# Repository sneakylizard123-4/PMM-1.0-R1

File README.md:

# PMM-1.0-R1 (Power Management Module)

A USB-C battery management module with charging, fuel gauging, and a switched 5V output.

## Custom Features

- BQ25895 2A buck charger with I2C control
- BQ27441-G1 fuel gauge
- TPS61089 boost converter for 5V output
- TPS22917 load
- TLV75733 3.3V LDO
- STM32C031C4T6 MCU
- 4-layer PCB, 50x30mm

## PCB Design

this board is designed to fit on a breadboard without much hassle
it is a 4-layer pcb with an inner ground layer

## Firmware

PlatformIO project using internal 48MHz oscillator (no crystal).

- I2C1 (PA9/PA10): BQ25895 charger at 0x6B, BQ27441 fuel gauge at 0x55
- USART2 (PA2/PA3): 115200 debug/status output
- ADC1 (PA8): VBUS monitoring
- GPIO: load switch (PA0), charger CE (PA4), LED (PA6), SHDN (PA11), FORCE_ON (PA12)

Flash with PlatformIO:

```
pio run -t upload
```

## BOM (Bill of Materials)

| Ref | Value | LCSC # | MPN | Manufacturer | Footprint | Qty | Unit $ | Ext $ | Link |
|-----|-------|--------|-----|--------------|-----------|-----|--------|-------|------|
| C1-C3,C8,C10 | 47uF 1210 16V X5R | C6783889 | 1210X476M160CT | Walsin | 1210 | 5 | 0.0900 | 0.4500 | [LCSC](https://www.lcsc.com/product-detail/C6783889.html) |
| C4,C7,C14,C27,C29 | 100nF 0402 25V X7R | C56392 | 0402B104K250NT | FH(Guangdong Fenghua) | 0402 | 5 | 0.0115 | 0.0575 | [LCSC](https://www.lcsc.com/product-detail/C56392.html) |
| C5 | 100nF 0805 50V X7R | C83055 | 0805B104K500CT | Walsin | 0805 | 1 | 0.0100 | 0.0100 | [LCSC](https://www.lcsc.com/product-detail/C83055.html) |
| C6,C22,C23,C28 | 10uF 0603 10V X5R | C19702 | CL10A106KP8NNNC | Samsung | 0603 | 4 | 0.0065 | 0.0260 | [LCSC](https://www.lcsc.com/product-detail/C19702.html) |
| C9 | 24pF 0402 C0G | C2242874 | C0402C240J4GACTU | KEMET | 0402 | 1 | 0.0100 | 0.0100 | [LCSC](https://www.lcsc.com/product-detail/C2242874.html) |
| C11 | 560pF 0402 C0G 50V | C3895255 | C0402C0G500-561FNP | Venkel | 0402 | 1 | 0.0313 | 0.0313 | [LCSC](https://www.lcsc.com/product-detail/C3895255.html) |
| C12,C19 | 100nF 0805 50V X7R | C83055 | 0805B104K500CT | Walsin | 0805 | 2 | 0.0100 | 0.0200 | [LCSC](https://www.lcsc.com/product-detail/C83055.html) |
| C13,C18 | 10uF 0805 10V X7R | C396720 | 0805B106K100CT | Walsin | 0805 | 2 | 0.0950 | 0.1900 | [LCSC](https://www.lcsc.com/product-detail/C396720.html) |
| C15 | 47uF 0805 10V X5R | C6119904 | CGA0805X5R476M100MT | HRE | 0805 | 1 | 0.1000 | 0.1000 | [LCSC](https://www.lcsc.com/product-detail/C6119904.html) |
| C16 | 1uF 0805 16V X7R | C2991444 | 0805B105K160CT-C | Walsin | 0805 | 1 | 0.0230 | 0.0230 | [LCSC](https://www.lcsc.com/product-detail/C2991444.html) |
| C17 | 0.47uF 0402 10V X5R | C47339 | CL05A474KP5NNNC | Samsung | 0402 | 1 | 0.0200 | 0.0200 | [LCSC](https://www.lcsc.com/product-detail/C47339.html) |
| C20 | 47nF 0603 25V X7R | C3881195 | C0603C473J3RAC7867 | KEMET | 0603 | 1 | 0.0100 | 0.0100 | [LCSC](https://www.lcsc.com/product-detail/C3881195.html) |
| C21 | 4.7uF 0402 6.3V X5R | C340648 | 0402X475M6R3CT | Walsin | 0402 | 1 | 0.0240 | 0.0240 | [LCSC](https://www.lcsc.com/product-detail/C340648.html) |
| C24,C25 | 1uF 0603 16V X7R | C106248 | CC0603KRX7R7BB105 | YAGEO | 0603 | 2 | 0.0310 | 0.0620 | [LCSC](https://www.lcsc.com/product-detail/C106248.html) |
| C26 | 100nF 0603 50V X7R | C14663 | CC0603KRX7R9BB104 | YAGEO | 0603 | 1 | 0.0100 | 0.0100 | [LCSC](https://www.lcsc.com/product-detail/C14663.html) |
| D1-D3 | LED 0603 emerald green | C7429914 | NCD0603G3 | NATIONSTAR | 0603 | 3 | 0.0080 | 0.0240 | [LCSC](https://www.lcsc.com/product-detail/C7429914.html) |
| L1 | 470nH shielded power inductor | C18221164 | XFL4015-471MEC | Coilcraft | SMD 4x4mm | 1 | 1.5000 | 1.5000 | [LCSC](https://www.lcsc.com/product-detail/C18221164.html) |
| L2 | 2.2uH shielded power inductor 8A | C122469 | XFL4020-222MEC | Coilcraft | SMD 4x4mm | 1 | 1.5000 | 1.5000 | [LCSC](https://www.lcsc.com/product-detail/C122469.html) |
| R1,R16,R19,R20 | 10k 0603 1% | C98220 | RC0603FR-0710KL | YAGEO | 0603 | 4 | 0.0100 | 0.0400 | [LCSC](https://www.lcsc.com/product-detail/C98220.html) |
| R2 | 309k 0402 1% | C171694 | RC0402FR-07309KL | YAGEO | 0402 | 1 | 0.0100 | 0.0100 | [LCSC](https://www.lcsc.com/product-detail/C171694.html) |
| R3 | 133k 0402 1% | C3015855 | SCR0402F133K | VO | 0402 | 1 | 0.0100 | 0.0100 | [LCSC](https://www.lcsc.com/product-detail/C3015855.html) |
| R4 | 28.7k 0402 1% | C185433 | RC0402FR-0728K7L | YAGEO | 0402 | 1 | 0.0100 | 0.0100 | [LCSC](https://www.lcsc.com/product-detail/C185433.html) |
| R5 | 240k 0603 1% | C137765 | RC0603FR-07240KL | YAGEO | 0603 | 1 | 0.0100 | 0.0100 | [LCSC](https://www.lcsc.com/product-detail/C137765.html) |
| R6 | 76.8k 0402 1% | C185396 | RC0402FR-0776K8L | YAGEO | 0402 | 1 | 0.0100 | 0.0100 | [LCSC](https://www.lcsc.com/product-detail/C185396.html) |
| R7 | 100k 0402 1% | C60491 | RC0402FR-07100KL | YAGEO | 0402 | 1 | 0.0060 | 0.0060 | [LCSC](https://www.lcsc.com/product-detail/C60491.html) |
| R8 | 100k 0603 1% | C14675 | RC0603FR-07100KL | YAGEO | 0603 | 1 | 0.0100 | 0.0100 | [LCSC](https://www.lcsc.com/product-detail/C14675.html) |
| R9 | 0.010 ohm 1% 2512 3W shunt | C520398 | LCSR2512FR010Q9L | RESI | 2512 | 1 | 0.1000 | 0.1000 | [LCSC](https://www.lcsc.com/product-detail/C520398.html) |
| R10-R14 | 10k 0402 1% | C60490 | RC0402FR-0710KL | YAGEO | 0402 | 5 | 0.0100 | 0.0500 | [LCSC](https://www.lcsc.com/product-detail/C60490.html) |
| R15 | 130 ohm 0805 1% | C273821 | RC0805FR-07130RL | YAGEO | 0805 | 1 | 0.0100 | 0.0100 | [LCSC](https://www.lcsc.com/product-detail/C273821.html) |
| R17 | 5.23k 0402 1% | C477746 | RC0402FR-075K23L | YAGEO | 0402 | 1 | 0.0100 | 0.0100 | [LCSC](https://www.lcsc.com/product-detail/C477746.html) |
| R18 | 30.1k 0402 1% | C138009 | RC0402FR-0730K1L | YAGEO | 0402 | 1 | 0.0100 | 0.0100 | [LCSC](https://www.lcsc.com/product-detail/C138009.html) |
| R21,R22 | 4.7k 0402 1% | C105871 | RC0402FR-074K7L | YAGEO | 0402 | 2 | 0.0100 | 0.0200 | [LCSC](https://www.lcsc.com/product-detail/C105871.html) |
| TH1 | 10k NTC thermistor 0402 | C77131 | NCP15XH103F03RC | muRata | 0402 | 1 | 0.0266 | 0.0266 | [LCSC](https://www.lcsc.com/product-detail/C77131.html) |
| U1 | TPS61089RNRR boost converter | C165129 | TPS61089RNRR | Texas Instruments | VQFN-11 | 1 | 0.5800 | 0.5800 | [LCSC](https://www.lcsc.com/product-detail/C165129.html) |
| U2 | TPS22917DBVR load switch | C2681320 | TPS22917DBVR | Texas Instruments | SOT-23-6 | 1 | 0.4600 | 0.4600 | [LCSC](https://www.lcsc.com/product-detail/C2681320.html) |
| U3 | BQ27441DRZR-G1B fuel gauge | C473374 | BQ27441DRZR-G1B | Texas Instruments | SON-12 | 1 | 2.7600 | 2.7600 | [LCSC](https://www.lcsc.com/product-detail/C473374.html) |
| U4 | BQ25895RTWR charger | C80200 | BQ25895RTWR | Texas Instruments | WQFN-24 | 1 | 2.1700 | 2.1700 | [LCSC](https://www.lcsc.com/product-detail/C80200.html) |
| U5 | TLV75733PDBVR 3.3V LDO | C485517 | TLV75733PDBVR | Texas Instruments | SOT-23-5 | 1 | 0.1950 | 0.1950 | [LCSC](https://www.lcsc.com/product-detail/C485517.html) |
| U6 | STM32C031C4T6 MCU | C5456207 | STM32C031C4T6 | STMicroelectronics | LQFP-48 | 1 | 1.6700 | 1.6700 | [LCSC](https://www.lcsc.com/product-detail/C5456207.html) |
| PCB | Bare PCB 50x30mm 4-layer | - | - | - | - | 1 | 2.5000 | 2.5000 | - |
| **Total** | - | - | - | - | - | **64** | - | **14.7354** | - |

Full BOM CSV: [BOM.csv](BOM.csv)

## Production

This board is designed for a standard 4-layer PCB fab:
- 4 layers
- HASL Lead Free
- 1.6mm board

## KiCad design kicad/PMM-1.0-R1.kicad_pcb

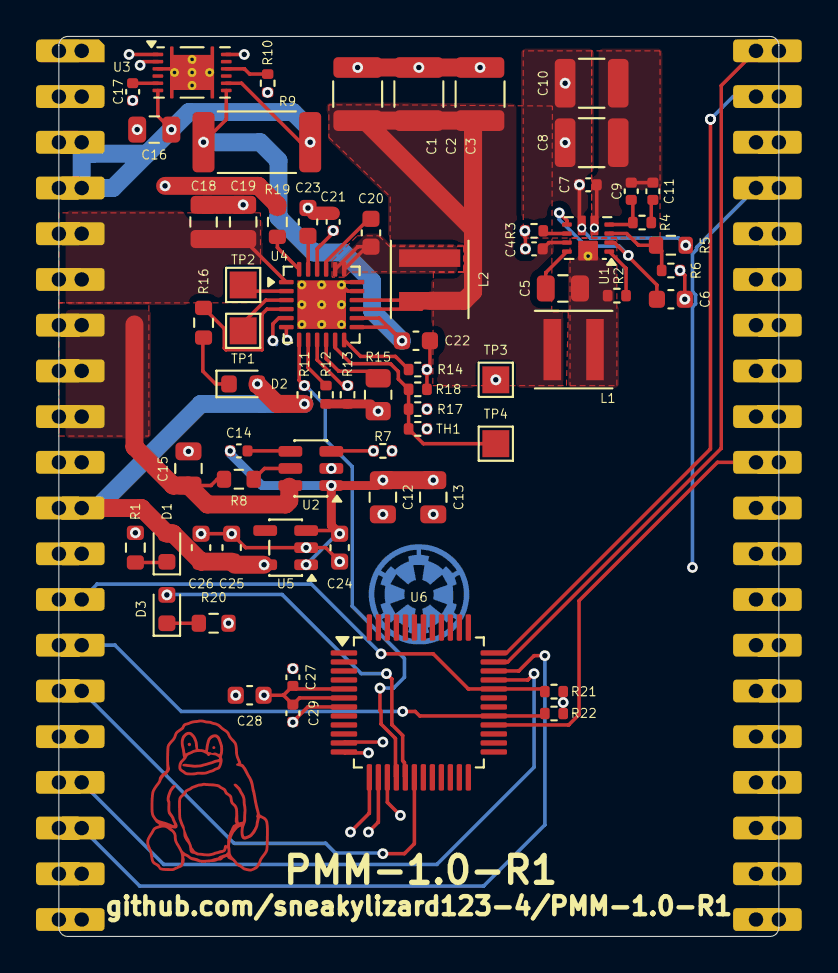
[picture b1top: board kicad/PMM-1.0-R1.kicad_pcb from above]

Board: 4 copper layers, 40.0 x 50.0 mm, 68 parts (0 on the bottom side), 50 nets.

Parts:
A1: PMM
C1, C2, C3, C8, C10: 47uF; C_1210_3225Metric
C4, C7, C14, C27, C29: 100nF; C_0402_1005Metric
C5: 0.1uF; C_0805_2012Metric
C6, C22, C23, C28: 10uF; C_0603_1608Metric
C9: 24pF; C_0402_1005Metric
C11: 560pF; C_0402_1005Metric
C12, C19: 100nF; C_0805_2012Metric
C13, C18: 10uF; C_0805_2012Metric
C15: 47uF; C_0805_2012Metric
C16: 1uF; C_0805_2012Metric
C17: 0.47uF; C_0402_1005Metric
C20: 47nF; C_0603_1608Metric
C21: 4.7uF; C_0402_1005Metric
C24, C25: 1uF; C_0603_1608Metric
C26: 100nF; C_0603_1608Metric
D1, D2, D3: LED; LED_0603_1608Metric
L1: 470nH Coilcraft XFL4015-471MEC; L_Coilcraft_XxL4020
L2: 2.2uH Coilcraft XAL4020-222MEC; L_Coilcraft_XxL4020
R1, R16, R19, R20: 10k; R_0603_1608Metric
R2: 309k; R_0402_1005Metric
R3: 133k; R_0402_1005Metric
R4: 28.7k; R_0402_1005Metric
R5: 240k; R_0603_1608Metric
R6: 76.8k; R_0402_1005Metric
R7: 100k; R_0402_1005Metric
R8: 100k; R_0603_1608Metric
R9: 0.010 1%; R_2512_6332Metric
R10, R11, R12, R13, R14: 10k; R_0402_1005Metric
R15: 130 1%; R_0805_2012Metric
R17: 5.23k; R_0402_1005Metric
R18: 30.1k; R_0402_1005Metric
R21, R22: 4.7k; R_0402_1005Metric
TH1: 10k NTC; R_0402_1005Metric
TP1, TP2, TP3, TP4: TestPoint; TestPoint_Pad_1.5x1.5mm
U1: TPS61089; Texas_VQFN-RNR0011A-11
U2: TPS22917DBV; SOT-23-6
U3: BQ27441-G1; Texas_S-PDSO-N12
U4: BQ25895RTW; Texas_RTW_WQFN-24-1EP_4x4mm_P0.5mm_EP2.7x2.7mm_ThermalVias
U5: TLV75733PDBV; SOT-23-5
U6: STM32C031C4T6; LQFP-48_7x7mm_P0.5mm

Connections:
5V_OUT: A1.7 (5V_OUT), A1.8 (5V_OUT), A1.9 (5V_OUT), C15.1, R8.1, U2.6 (VOUT)
+3.3V: A1.11 (3V3), C25.1, C26.1, C27.1, C28.1, C29.1, D1.2 (A), D2.2 (A), R11.1, R19.1, R21.1, R22.1, U5.5 (OUT), U6.5 (VREF+), U6.6 (VDD)
/BQ25895/BAT+: C22.1, R9.1, U3.7 (SRN), U4.13 (BAT), U4.14 (BAT)
/BQ25895/BQ25895_VOUT: C1.1, C2.1, C3.1, C4.1, L1.1, L2.2, U1.9 (VIN), U4.15 (SYS), U4.16 (SYS)
/TPS61089/TPS61089_VOUT: C7.1, C8.1, C10.1, C12.1, C13.1, C14.1, C24.1, R5.1, U1.6 (VOUT), U2.1 (VIN), U5.1 (IN), U5.3 (EN)
ADC_IN: A1.31 (ADC_IN), U6.28 (PA8)
BQ25895_CE: R13.1, U4.9 (~CE), U6.15 (PA4)
BQ25895_INT: R11.2, U4.7 (~INT), U6.16 (PA5)
BQ25895_OTG: R12.1, U4.8 (OTG)
BQ27441_GPOUT: U3.12 (GPOUT), U6.12 (PA1)
FORCE_ON: A1.18 (FORCE_ON), U6.34 (PA12)
unnamed: C11.1, R4.2
unnamed: C20.1, L2.1, U4.19 (SW), U4.20 (SW)
unnamed: D1.1 (K), R1.1
unnamed: D2.1 (K), R16.1
unnamed: D3.2 (A), U6.17 (PA6)
unnamed: D3.1 (K), R20.1
unnamed: C5.2, U1.10 (BOOT)
unnamed: C9.1, R4.1, U1.4 (COMP)
unnamed: C6.1, U1.2 (VCC), U1.7 (EN)
unnamed: R5.2, R6.1, U1.3 (FB)
unnamed: R2.2, U1.1 (FSW)
unnamed: R3.1, U1.8 (ILIM)
unnamed: C5.1, L1.2, R2.1, U1.11 (SW)
unnamed: C14.2, U2.4 (CT)
unnamed: R8.2, U2.5 (QOD)
unnamed: R10.1, U3.10 (BIN)
unnamed: C17.1, U3.5 (V_{DD})
unnamed: C20.2, U4.21 (BTST)
unnamed: TP2.1 (1_1), U4.2 (D+)
unnamed: TP1.1 (1_1), U4.3 (D-)
unnamed: R19.2, U4.24 (DSEL)
unnamed: R15.1, U4.10 (ILIM)
unnamed: C23.1, U4.23 (PMID)
unnamed: C21.1, R17.1, U4.22 (REGN)
unnamed: R16.2, U4.4 (STAT)
unnamed: R17.2, R18.1, TH1.1, TP4.1 (1_1), U4.11 (TS)
unnamed: R14.1, U4.12 (~QON)
PACK+: A1.3 (VBAT+), A1.4 (VBAT+), C16.1, R9.2, U3.6 (BAT), U3.8 (SRP)
PACK-: A1.1 (GND), A1.2 (GND), A1.10 (GND), A1.12 (GND), A1.21 (GND), A1.22 (GND), C1.2, C2.2, C3.2, C4.2, C6.2, C7.2, C8.2, C9.2, C10.2, C11.2, C12.2, C13.2, C15.2, C16.2, C17.2, C18.2, C19.2, C21.2, C22.2, C23.2, C24.2, C25.2, C26.2, C27.2, C28.2, C29.2, R1.2, R3.2, R6.2, R7.2, R10.2, R12.2, R13.2, R14.2, R15.2, R18.2, R20.2, TH1.2, TP3.1 (1_1), U1.5 (GND), U2.2 (GND), U3.3 (V_{SS}), U3.13 (PAD), U4.17 (PGND), U4.18 (PGND), U4.25 (PGND), U5.2 (GND), U6.7 (VSS)
PMM_INT: A1.15 (PMM_INIT), U6.18 (PA7)
SCL: A1.14 (SCL), R22.2, U3.2 (SCL), U4.5 (SCL), U6.29 (PA9)
SDA: A1.13 (SDA), R21.2, U3.1 (SDA), U4.6 (SDA), U6.32 (PA10)
SHDN: A1.17 (SHDN), U6.33 (PA11)
SWCLK: A1.39 (SWCLK), U6.36 (PA14)
SWDIO: A1.40 (SWDIO), U6.35 (PA13)
TPS2291_ON: R7.1, U2.3 (ON), U6.11 (PA0)
UART_RX: A1.36 (UART_RX), U6.14 (PA3)
UART_TX: A1.37 (UART_TX), U6.13 (PA2)
VBUS_5V_IN: A1.5 (VBAT_5V_IN), A1.6 (VBAT_5V_IN), C18.1, C19.1, U4.1 (VBUS)

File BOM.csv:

"Ref","Value","Footprint","Qty","Manufacturer","MPN"
"A1","PMM","PMM:PMM","1","",""
"C1-C3,C8,C10","47uF","Capacitor_SMD:C_1210_3225Metric","5","",""
"C4,C7,C14,C27,C29","100nF","Capacitor_SMD:C_0402_1005Metric","5","",""
"C5","0.1uF","Capacitor_SMD:C_0805_2012Metric","1","",""
"C6,C22,C23,C28","10uF","Capacitor_SMD:C_0603_1608Metric","4","",""
"C9","24pF","Capacitor_SMD:C_0402_1005Metric","1","",""
"C11","560pF","Capacitor_SMD:C_0402_1005Metric","1","",""
"C12,C19","100nF","Capacitor_SMD:C_0805_2012Metric","2","",""
"C13,C18","10uF","Capacitor_SMD:C_0805_2012Metric","2","",""
"C15","47uF","Capacitor_SMD:C_0805_2012Metric","1","",""
"C16","1uF","Capacitor_SMD:C_0805_2012Metric","1","",""
"C17","0.47uF","Capacitor_SMD:C_0402_1005Metric","1","",""
"C20","47nF","Capacitor_SMD:C_0603_1608Metric","1","",""
"C21","4.7uF","Capacitor_SMD:C_0402_1005Metric","1","",""
"C24,C25","1uF","Capacitor_SMD:C_0603_1608Metric","2","",""
"C26","100nF","Capacitor_SMD:C_0603_1608Metric","1","",""
"D1-D3","LED","LED_SMD:LED_0603_1608Metric","3","",""
"L1","470nH Coilcraft XFL4015-471MEC","Inductor_SMD:L_Coilcraft_XxL4020","1","",""
"L2","2.2uH Coilcraft XAL4020-222MEC","Inductor_SMD:L_Coilcraft_XxL4020","1","",""
"R1,R16,R19,R20","10k","Resistor_SMD:R_0603_1608Metric","4","",""
"R2","309k","Resistor_SMD:R_0402_1005Metric","1","",""
"R3","133k","Resistor_SMD:R_0402_1005Metric","1","",""
"R4","28.7k","Resistor_SMD:R_0402_1005Metric","1","",""
"R5","240k","Resistor_SMD:R_0603_1608Metric","1","",""
"R6","76.8k","Resistor_SMD:R_0402_1005Metric","1","",""
"R7","100k","Resistor_SMD:R_0402_1005Metric","1","",""
"R8","100k","Resistor_SMD:R_0603_1608Metric","1","",""
"R9","0.010 1%","Resistor_SMD:R_2512_6332Metric","1","",""
"R10-R14","10k","Resistor_SMD:R_0402_1005Metric","5","",""
"R15","130 1%","Resistor_SMD:R_0805_2012Metric","1","",""
"R17","5.23k","Resistor_SMD:R_0402_1005Metric","1","",""
"R18","30.1k","Resistor_SMD:R_0402_1005Metric","1","",""
"R21,R22","4.7k","Resistor_SMD:R_0402_1005Metric","2","",""
"TH1","10k NTC","Resistor_SMD:R_0402_1005Metric","1","",""
"TP1-TP4","TestPoint","TestPoint:TestPoint_Pad_1.5x1.5mm","4","",""
"U1","TPS61089","Package_DFN_QFN:Texas_VQFN-RNR0011A-11","1","",""
"U2","TPS22917DBV","Package_TO_SOT_SMD:SOT-23-6","1","",""
"U3","BQ27441-G1","Package_SON:Texas_S-PDSO-N12","1","",""
"U4","BQ25895RTW","Package_DFN_QFN:Texas_RTW_WQFN-24-1EP_4x4mm_P0.5mm_EP2.7x2.7mm_ThermalVias","1","",""
"U5","TLV75733PDBV","Package_TO_SOT_SMD:SOT-23-5","1","",""
"U6","STM32C031C4T6","Package_QFP:LQFP-48_7x7mm_P0.5mm","1","",""

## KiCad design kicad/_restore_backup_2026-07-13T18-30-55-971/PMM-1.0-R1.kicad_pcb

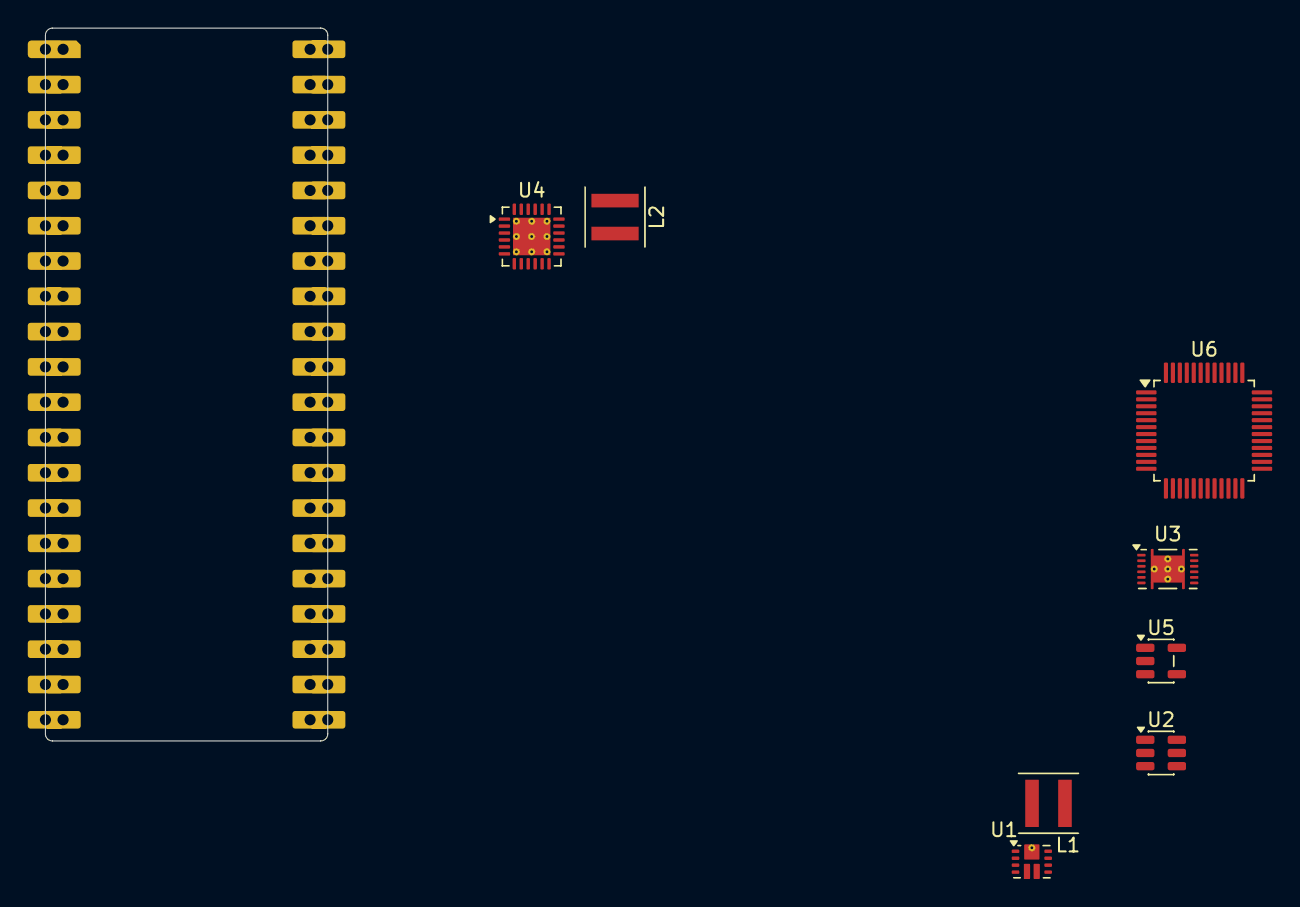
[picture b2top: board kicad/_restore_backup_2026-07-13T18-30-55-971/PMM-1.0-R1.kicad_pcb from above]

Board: 4 copper layers, 20.3 x 51.3 mm, 9 parts (0 on the bottom side), 26 nets, no tracks yet.

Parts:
A1: PMM
L1: 470nH Coilcraft XFL4015-471MEC; L_Coilcraft_XxL4020
L2: 2.2uH Coilcraft XAL4020-222MEC; L_Coilcraft_XxL4020
U1: TPS61089; Texas_VQFN-RNR0011A-11
U2: TPS22917DBV; SOT-23-6
U3: BQ27441-G1; Texas_S-PDSO-N12
U4: BQ25895RTW; Texas_RTW_WQFN-24-1EP_4x4mm_P0.5mm_EP2.7x2.7mm_ThermalVias
U5: TLV75733PDBV; SOT-23-5
U6: STM32C031C4T6; LQFP-48_7x7mm_P0.5mm

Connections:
5V_OUT: A1.7 (5V_OUT), A1.8 (5V_OUT), A1.9 (5V_OUT)
+3.3V: A1.11 (3V3), U5.5 (OUT), U6.5 (VREF+), U6.6 (VDD)
/BQ25895/BAT+: U3.7 (SRN), U4.13 (BAT), U4.14 (BAT)
/BQ25895/VOUT: L1.1, L2.2, U1.9 (VIN), U4.15 (SYS), U4.16 (SYS)
/TLV75733/VIN: U1.6 (VOUT), U2.1 (VIN), U5.1 (IN), U5.3 (EN)
ADC_IN: A1.31 (ADC_IN), U6.28 (PA8)
BATT+: A1.3 (VBAT+), A1.4 (VBAT+)
BATT-: A1.1 (GND), A1.2 (GND), A1.10 (GND), A1.12 (GND), A1.21 (GND), A1.22 (GND), U1.5 (GND), U2.2 (GND), U3.3 (V_{SS}), U3.13 (PAD), U4.17 (PGND), U4.18 (PGND), U4.25 (PGND), U5.2 (GND), U6.7 (VSS)
BQ25895_CE: U4.9 (~CE), U6.15 (PA4)
BQ25895_INT: U4.7 (~INT), U6.16 (PA5)
BQ27441_GPOUT: U3.12 (GPOUT), U6.12 (PA1)
FORCE_ON: A1.18 (FORCE_ON), U6.34 (PA12)
unnamed: L2.1, U4.19 (SW), U4.20 (SW)
unnamed: U1.2 (VCC), U1.7 (EN)
unnamed: L1.2, U1.11 (SW)
PACK+: U3.6 (BAT), U3.8 (SRP)
PMM_INT: A1.15 (PMM_INIT), U6.18 (PA7)
SCL: A1.14 (SCL), U3.2 (SCL), U4.5 (SCL), U6.29 (PA9)
SDA: A1.13 (SDA), U3.1 (SDA), U4.6 (SDA), U6.32 (PA10)
SHDN: A1.17 (SHDN), U6.33 (PA11)
SWCLK: A1.39 (SWCLK), U6.36 (PA14)
SWDIO: A1.40 (SWDIO), U6.35 (PA13)
TPS2291_ON: U2.3 (ON), U6.11 (PA0)
UART_RX: A1.36 (UART_RX), U6.14 (PA3)
UART_TX: A1.37 (UART_TX), U6.13 (PA2)
VBUS_5V_IN: A1.5 (VBAT_5V_IN), A1.6 (VBAT_5V_IN)

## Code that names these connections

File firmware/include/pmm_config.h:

/**
 * @file pmm_config.h
 * @brief PMM-1.0-R1 hardware configuration and pin definitions.
 *
 * Power Management Module — STM32C031C4T6 (LQFP-48, Cortex-M0+, 48 MHz HSI).
 */

#ifndef PMM_CONFIG_H
#define PMM_CONFIG_H

#include "stm32c0xx_hal.h"

/* ── I2C addresses (7-bit) ─────────────────────────────────────────────── */
#define BQ25895_I2C_ADDR        0x6BU
#define BQ27441_I2C_ADDR        0x55U

/* ── I2C bus ───────────────────────────────────────────────────────────── */
#define PMM_I2C                 I2C1
#define PMM_I2C_SCL_PORT        GPIOA
#define PMM_I2C_SCL_PIN         GPIO_PIN_9   /* PA9  — I2C1_SCL */
#define PMM_I2C_SDA_PORT        GPIOA
#define PMM_I2C_SDA_PIN         GPIO_PIN_10  /* PA10 — I2C1_SDA */
#define PMM_I2C_SPEED           400000U      /* 400 kHz fast-mode */

/* ── UART (debug) ─────────────────────────────────────────────────────── */
#define PMM_UART                USART2
#define PMM_UART_TX_PORT        GPIOA
#define PMM_UART_TX_PIN         GPIO_PIN_2   /* PA2 — USART2_TX */
#define PMM_UART_RX_PORT        GPIOA
#define PMM_UART_RX_PIN         GPIO_PIN_3   /* PA3 — USART2_RX */
#define PMM_UART_BAUD           115200U

/* ── ADC ───────────────────────────────────────────────────────────────── */
#define PMM_ADC                 ADC1
#define PMM_ADC_CH              ADC_CHANNEL_8   /* PA8 — ADC1_IN8 */
#define PMM_ADC_PORT            GPIOA
#define PMM_ADC_PIN             GPIO_PIN_8

/* ── GPIO outputs ──────────────────────────────────────────────────────── */
#define LOAD_SW_PORT            GPIOA
#define LOAD_SW_PIN             GPIO_PIN_0   /* PA0 — TPS22917 ON (active high) */

#define CHG_CE_PORT             GPIOA
#define CHG_CE_PIN              GPIO_PIN_4   /* PA4 — BQ25895 ~CE (active low) */

#define LED_PORT                GPIOA
#define LED_PIN                 GPIO_PIN_6   /* PA6 — D3 status LED (active high) */

#define PMM_INT_PORT            GPIOA
#define PMM_INT_PIN             GPIO_PIN_7   /* PA7 — PMM_INT (to host) */

#define SHDN_PORT               GPIOA
#define SHDN_PIN                GPIO_PIN_11  /* PA11 — SHDN control */

#define FORCE_ON_PORT           GPIOA
#define FORCE_ON_PIN            GPIO_PIN_12  /* PA12 — FORCE_ON control */

/* ── GPIO inputs ───────────────────────────────────────────────────────── */
#define BQ27441_INT_PORT        GPIOA
#define BQ27441_INT_PIN         GPIO_PIN_1   /* PA1 — BQ27441 GPOUT (active low) */

#define BQ25895_INT_PORT        GPIOA
#define BQ25895_INT_PIN         GPIO_PIN_5   /* PA5 — BQ25895 INT (active low) */

/* ── Clock configuration ───────────────────────────────────────────────── */
#define HSI_VALUE_HZ            48000000UL
#define SYSTEM_CLOCK_HZ         48000000UL

/* ── Timing constants (ms) ─────────────────────────────────────────────── */
#define LED_BLINK_PERIOD_MS     500U
#define POLL_INTERVAL_MS        1000U
#define STATUS_PRINT_MS         5000U
#define DEBOUNCE_MS             50U

/* ── Current sense resistor (10 mΩ) ───────────────────────────────────── */
#define SHUNT_RESISTANCE_MOHM   10U

#endif /* PMM_CONFIG_H */
